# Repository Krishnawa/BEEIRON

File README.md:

# BEEIRON
A JBC soldering station

You can see the BOM file by [clicking here](https://rawcdn.githack.com/Krishnawa/BEEIRON/8fc64078c1fd5ed8496f45e8a351d78156f50b11/BEEIRON%20v0.0.3/bom/ibom.html)

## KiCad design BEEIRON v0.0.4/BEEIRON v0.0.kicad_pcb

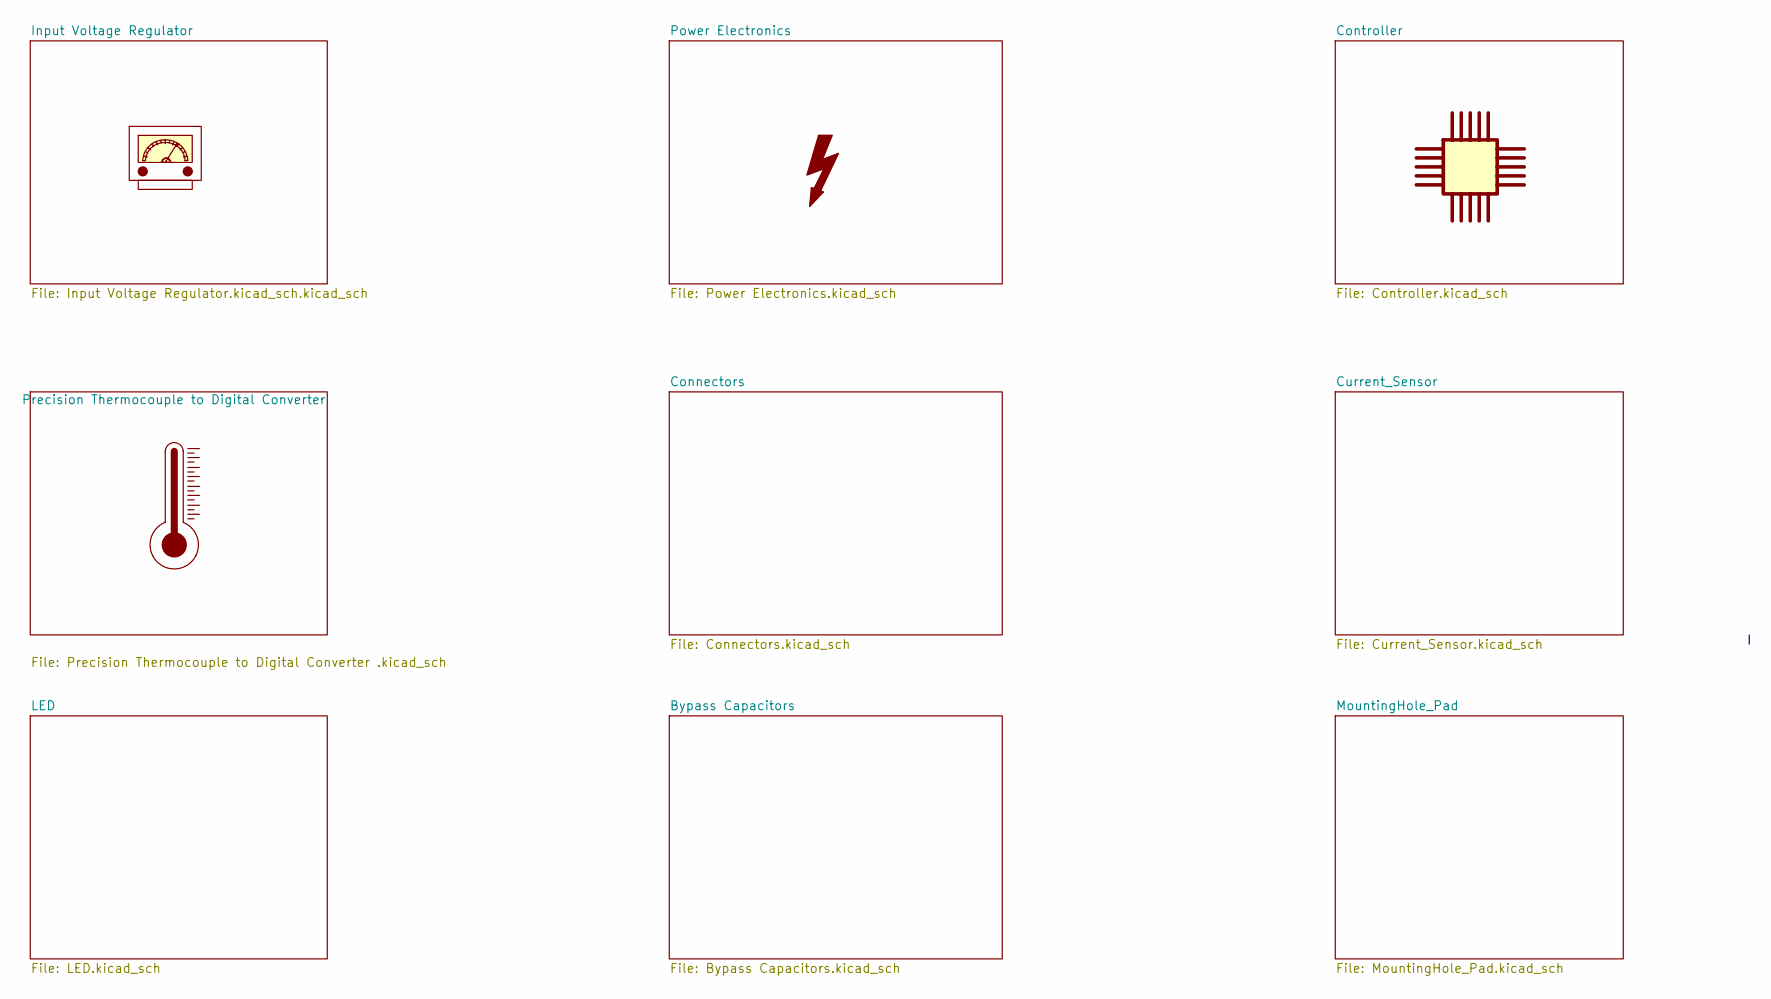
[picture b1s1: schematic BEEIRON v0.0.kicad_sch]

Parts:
MCU1: MCU; SolderJumper-2_P1.3mm_Open_TrianglePad1.0x1.5mm
U1: Regulator
U2: ThermoMeter

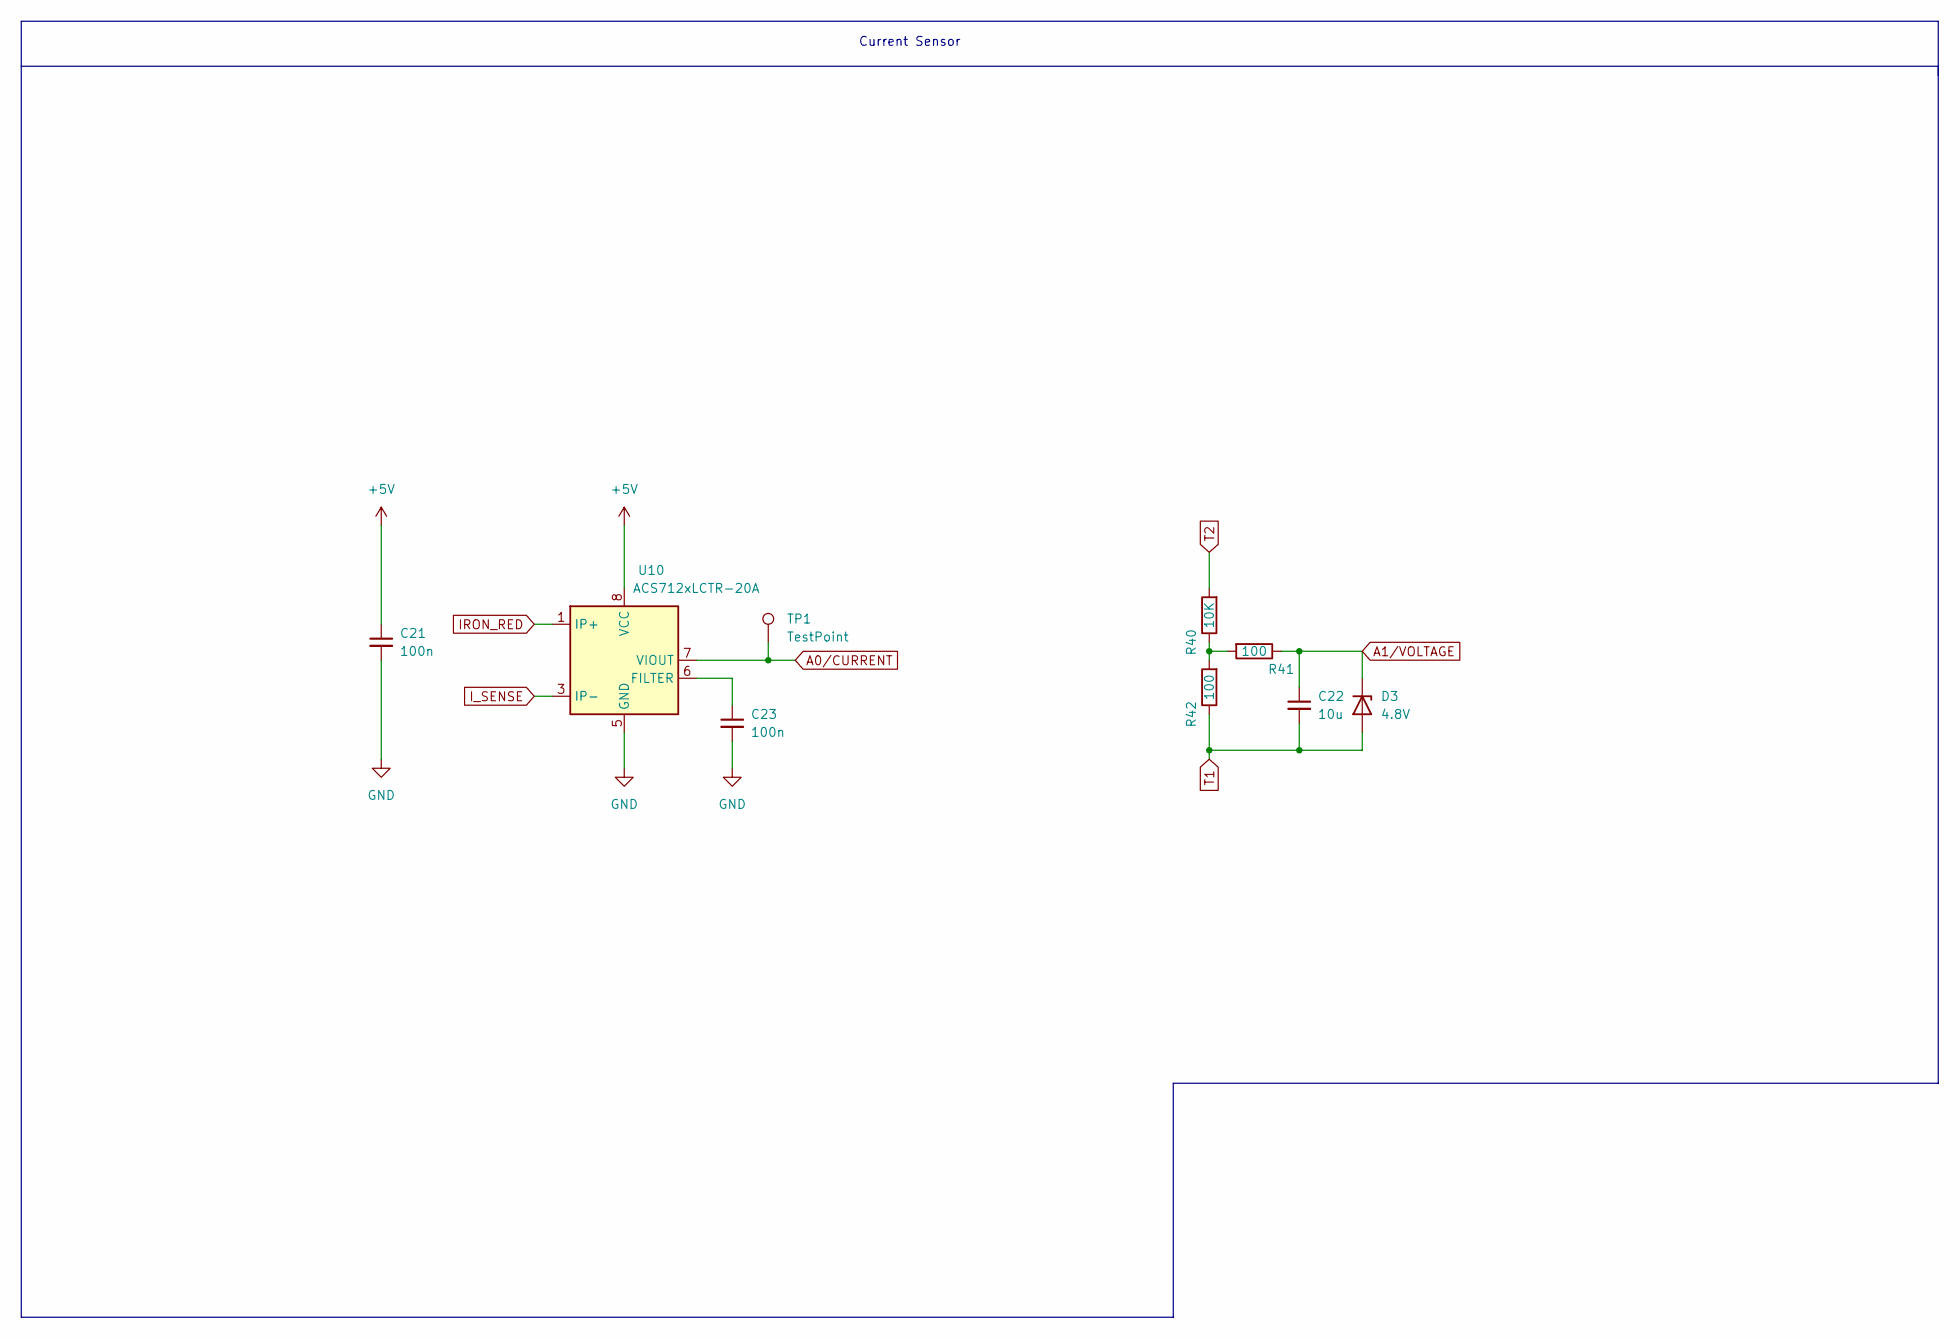
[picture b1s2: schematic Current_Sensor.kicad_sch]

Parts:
C21, C23: 100n; C_0805_2012Metric
C22: 10u; C_0805_2012Metric
D3: 4.8V; D_DO-35_SOD27_P10.16mm_Horizontal
R40: 10K; R_0805_2012Metric
R41, R42: 100; R_0805_2012Metric
TP1: TestPoint; TestPoint_Pad_2.5x2.5mm
U10: ACS712xLCTR-20A; SOIC-8_3.9x4.9mm_P1.27mm

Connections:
+5V: C21.1, U10.8 (VCC); also elsewhere on the board
A0/CURRENT: TP1.1, U10.7 (VIOUT); also elsewhere on the board
A1/VOLTAGE: C22.1, D3.1 (K), R41.1; also elsewhere on the board
GND: C21.2, C23.2, U10.5 (GND); also elsewhere on the board
IRON_RED: U10.1 (IP+), U10.2 (IP+); also elsewhere on the board
I_SENSE: U10.3 (IP-), U10.4 (IP-); also elsewhere on the board
unnamed: C23.1, U10.6 (FILTER)
unnamed: R40.1, R41.2, R42.2
T1: C22.2, D3.2 (A), R42.1; also elsewhere on the board
T2: R40.2; also elsewhere on the board

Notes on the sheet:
Current Sensor

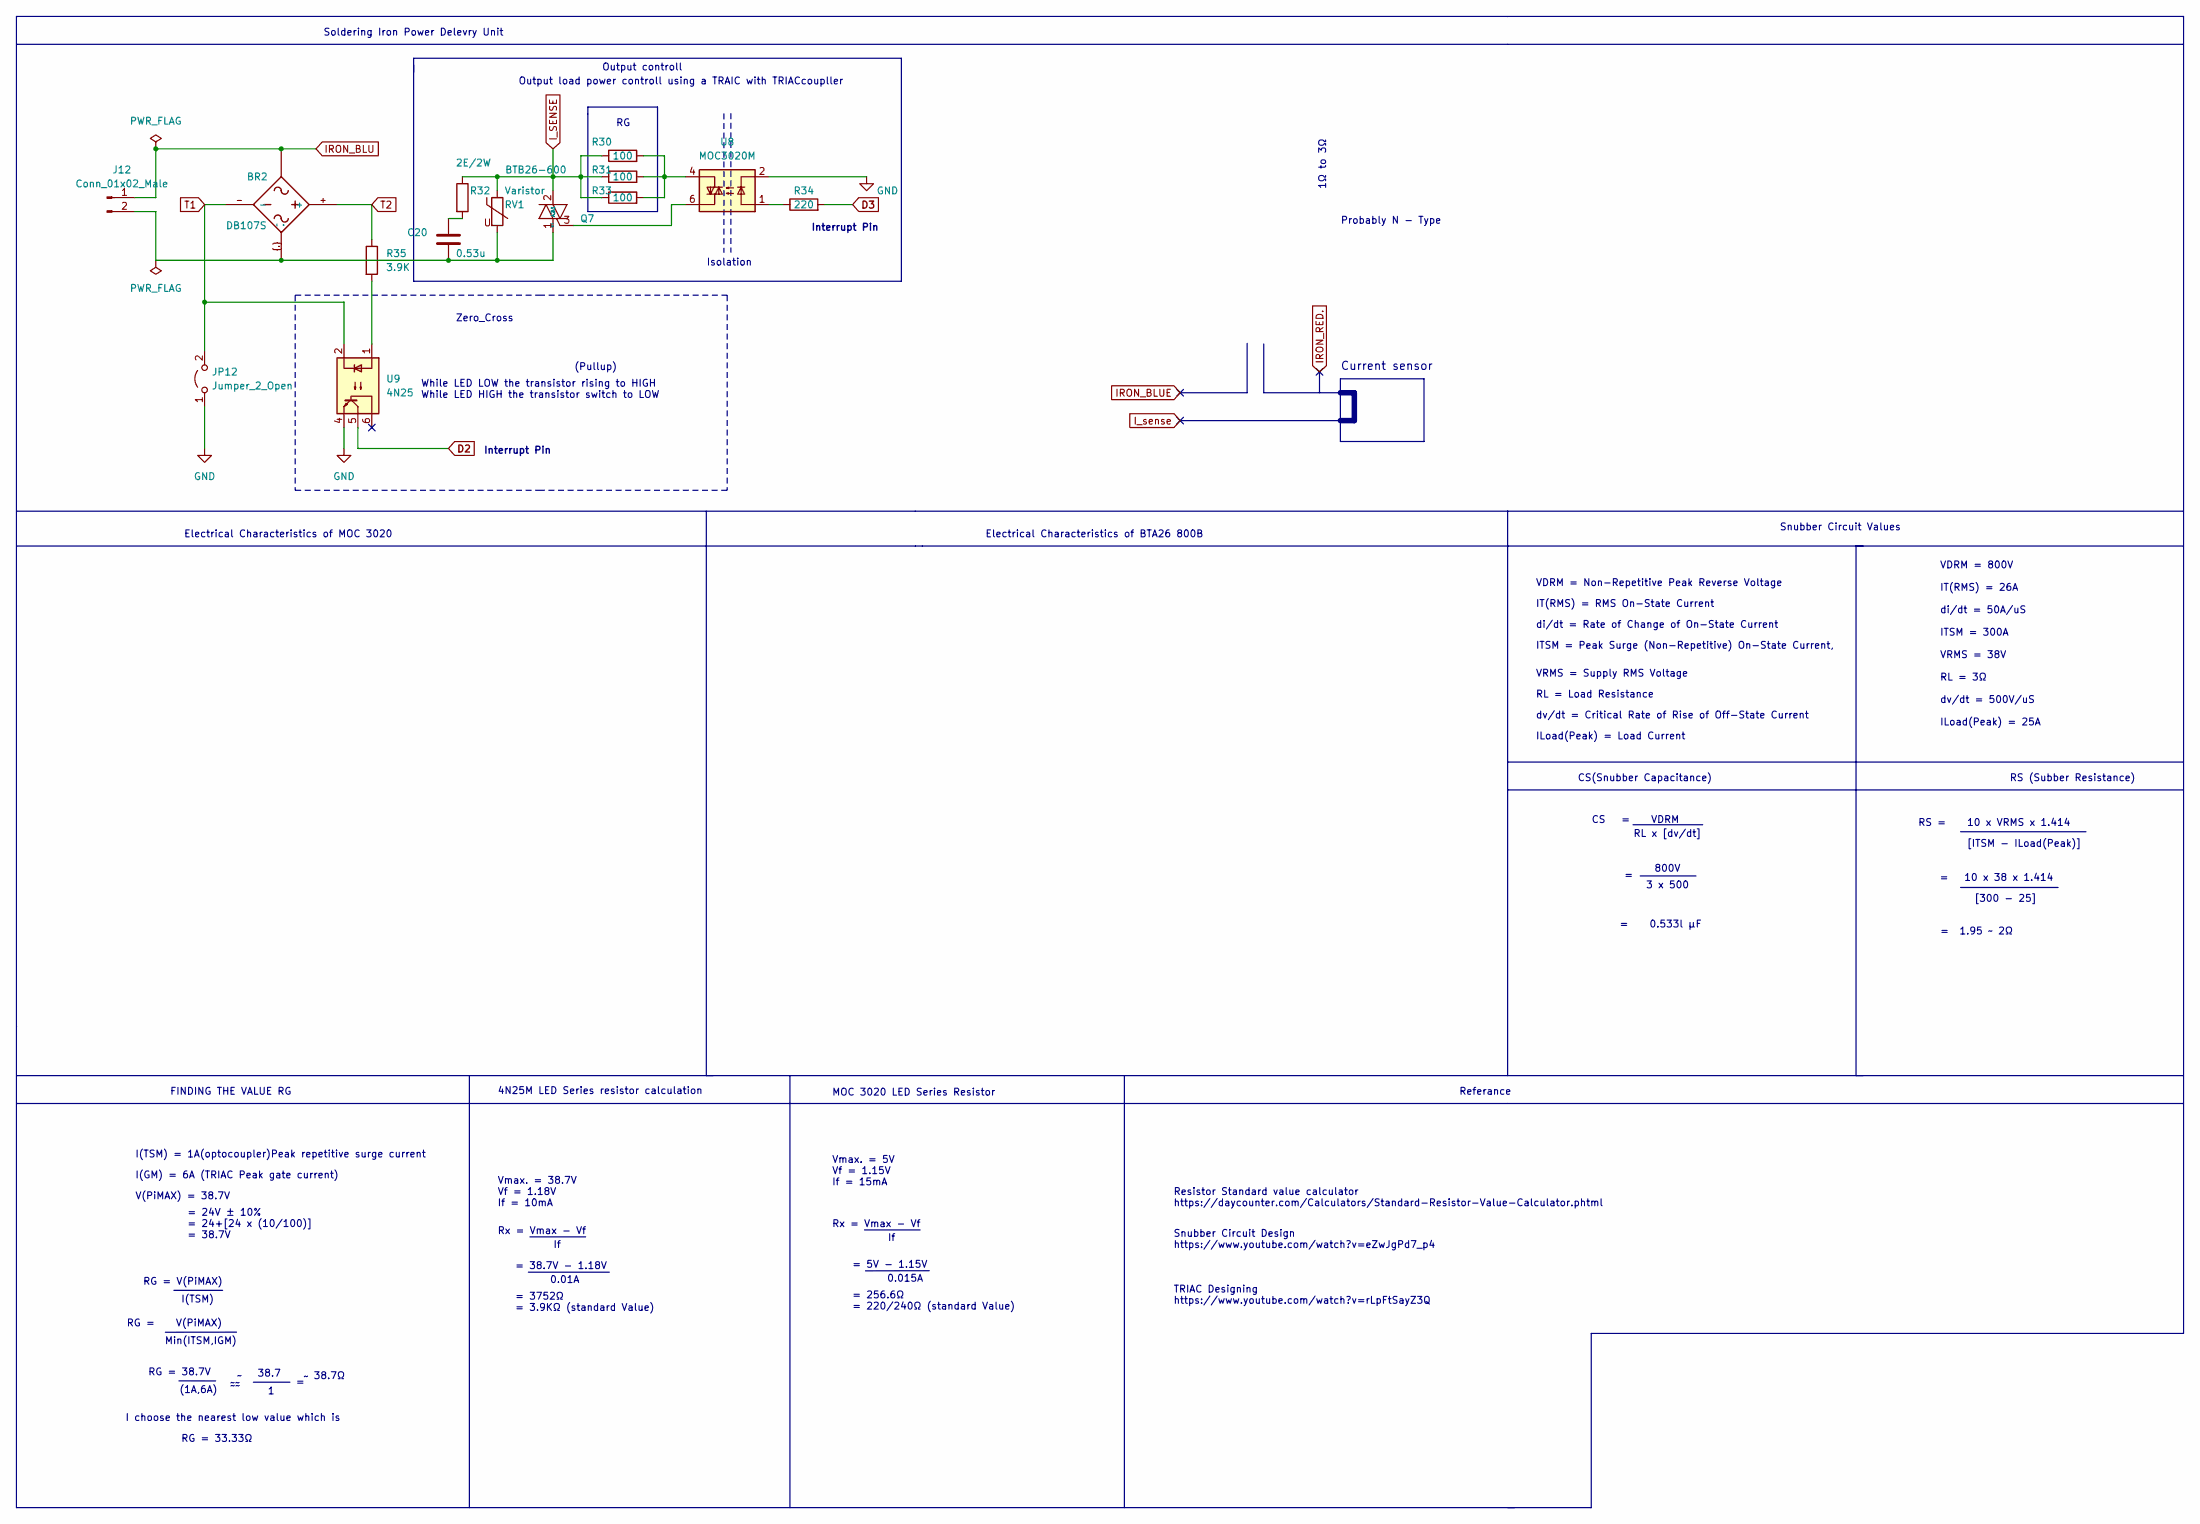
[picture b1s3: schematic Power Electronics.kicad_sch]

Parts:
BR2: DB107S; DIOB_DB107S
C20: 0.53u; C_Disc_D9.0mm_W5.0mm_P10.00mm
J12: Conn_01x02_Male; PhoenixContact_MSTBVA_2,5_2-G_1x02_P5.00mm_Vertical
JP12: Jumper_2_Open; SolderJumper-2_P1.3mm_Open_TrianglePad1.0x1.5mm
Q7: BTB26-600; TO-3P-3_Vertical
R30, R31, R33: 100; R_0805_2012Metric
R32: 2E/2W; R_Axial_DIN0411_L9.9mm_D3.6mm_P7.62mm_Vertical
R34: 220; R_0805_2012Metric
R35: 3.9K; R_0805_2012Metric
RV1: Varistor; RV_Disc_D12mm_W5.1mm_P7.5mm
U8: MOC3020M; DIP-6_W7.62mm_LongPads
U9: 4N25; DIP-6_W7.62mm

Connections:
D2: U9.5; also elsewhere on the board
D3: R34.2; also elsewhere on the board
GND: JP12.1 (A), U8.2, U9.4; also elsewhere on the board
IRON_BLU: BR2.~, BR2.~~, J12.1; also elsewhere on the board
I_SENSE: Q7.2 (A2), R30.1, R31.1, R32.1, R33.1, RV1.1; also elsewhere on the board
unnamed: BR2.~{.}, C20.2, J12.2, Q7.1 (A1), RV1.2
unnamed: C20.1, R32.2
unnamed: Q7.3 (G), U8.6
unnamed: R30.2, R31.2, R33.2, U8.4
unnamed: R34.1, U8.1
unnamed: R35.2, U9.1
T1: BR2.-, JP12.2 (B), U9.2; also elsewhere on the board
T2: BR2.+, R35.1; also elsewhere on the board

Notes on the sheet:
= 38.7V - 1.18V
Soldering Iron Power Delevry Unit
I(TSM) = 1A(optocoupler)Peak repetitive surge current
Output controll
= 3752Ω = 3.9KΩ (standard Value)
CS(Snubber Capacitance)
1Ω to 3Ω
Output load power controll using a TRAIC with TRIACcoupller
RL x [dv/dt]
VRMS = Supply RMS Voltage
Snubber Circuit Design https://www.youtube.com/watch?v=eZwJgPd7_p4
Rx = Vmax - Vf
0.015A
VDRM = Non−Repetitive Peak Reverse Voltage
RS (Subber Resistance)
FINDING THE VALUE RG
Resistor Standard value calculator https://daycounter.com/Calculators/Standard-Resistor-Value-Calculator.phtml
di/dt = Rate of Change of On−State Current
I choose the nearest low value which is
I(GM) = 6A (TRIAC Peak gate current)
IT(RMS) = RMS On−State Current
Zero_Cross
Isolation
I(TSM)
Referance
Min(ITSM,IGM)
CS = VDRM
VDRM = 800V IT(RMS) = 26A di/dt = 50A/uS ITSM = 300A VRMS = 38V RL = 3Ω dv/dt = 500V/uS ILoad(Peak) = 25A
(1A,6A)
RG = V(PiMAX)
RG = 33.33Ω
38.7
= 5V - 1.15V
Probably N - Type
[ITSM - ILoad(Peak)]
RL = Load Resistance
Current sensor
Interrupt Pin
ILoad(Peak) = Load Current
V(PiMAX) = 38.7V

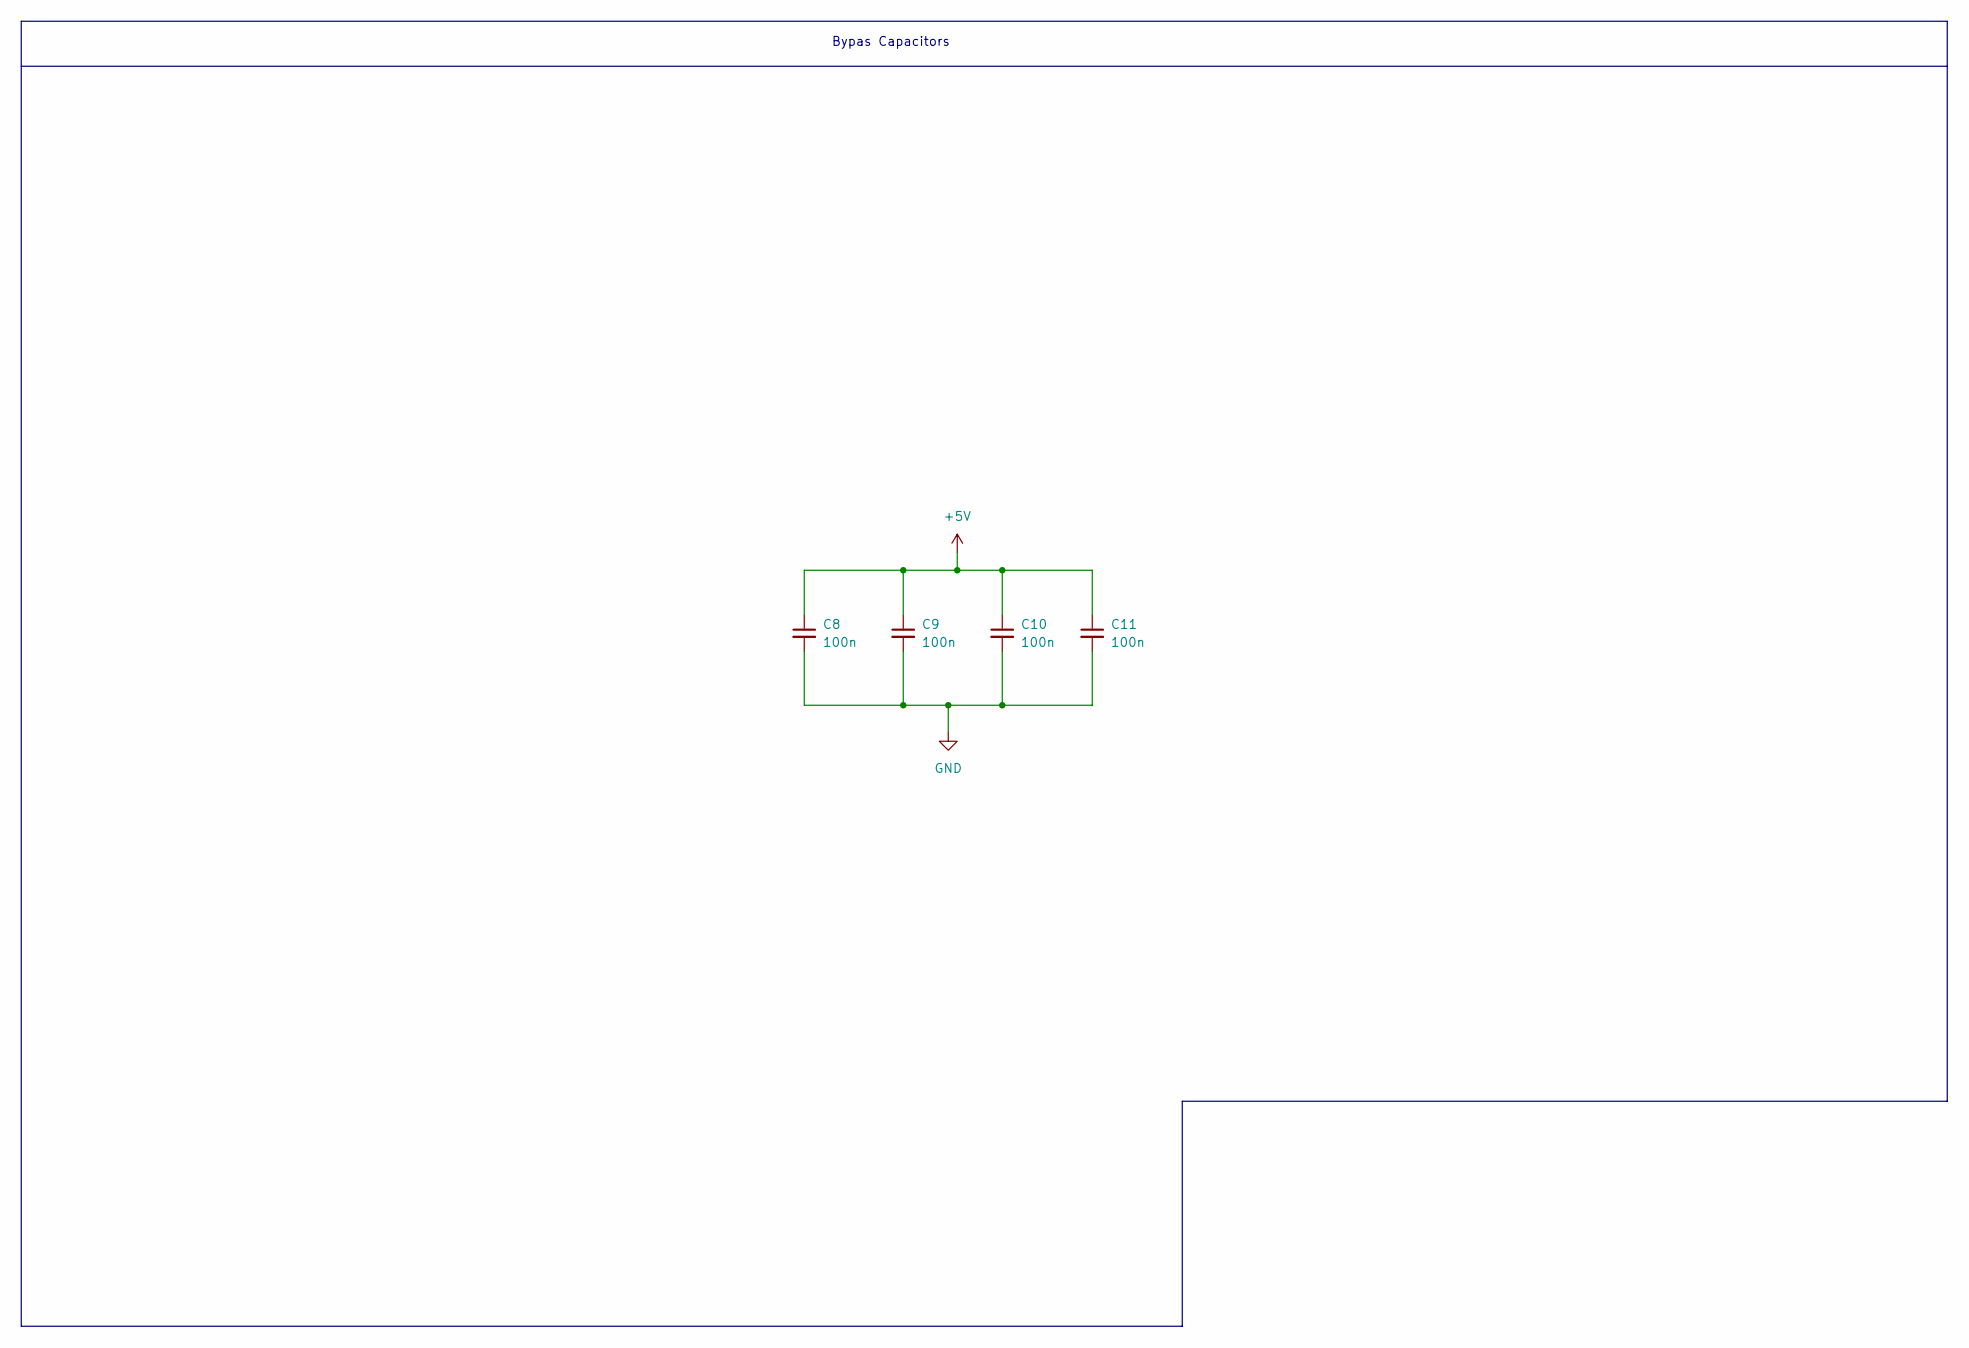
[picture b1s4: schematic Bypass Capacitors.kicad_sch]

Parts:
C8, C9, C10, C11: 100n; C_0805_2012Metric

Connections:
+5V: C8.1, C9.1, C10.1, C11.1; also elsewhere on the board
GND: C8.2, C9.2, C10.2, C11.2; also elsewhere on the board

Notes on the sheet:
Bypas Capacitors

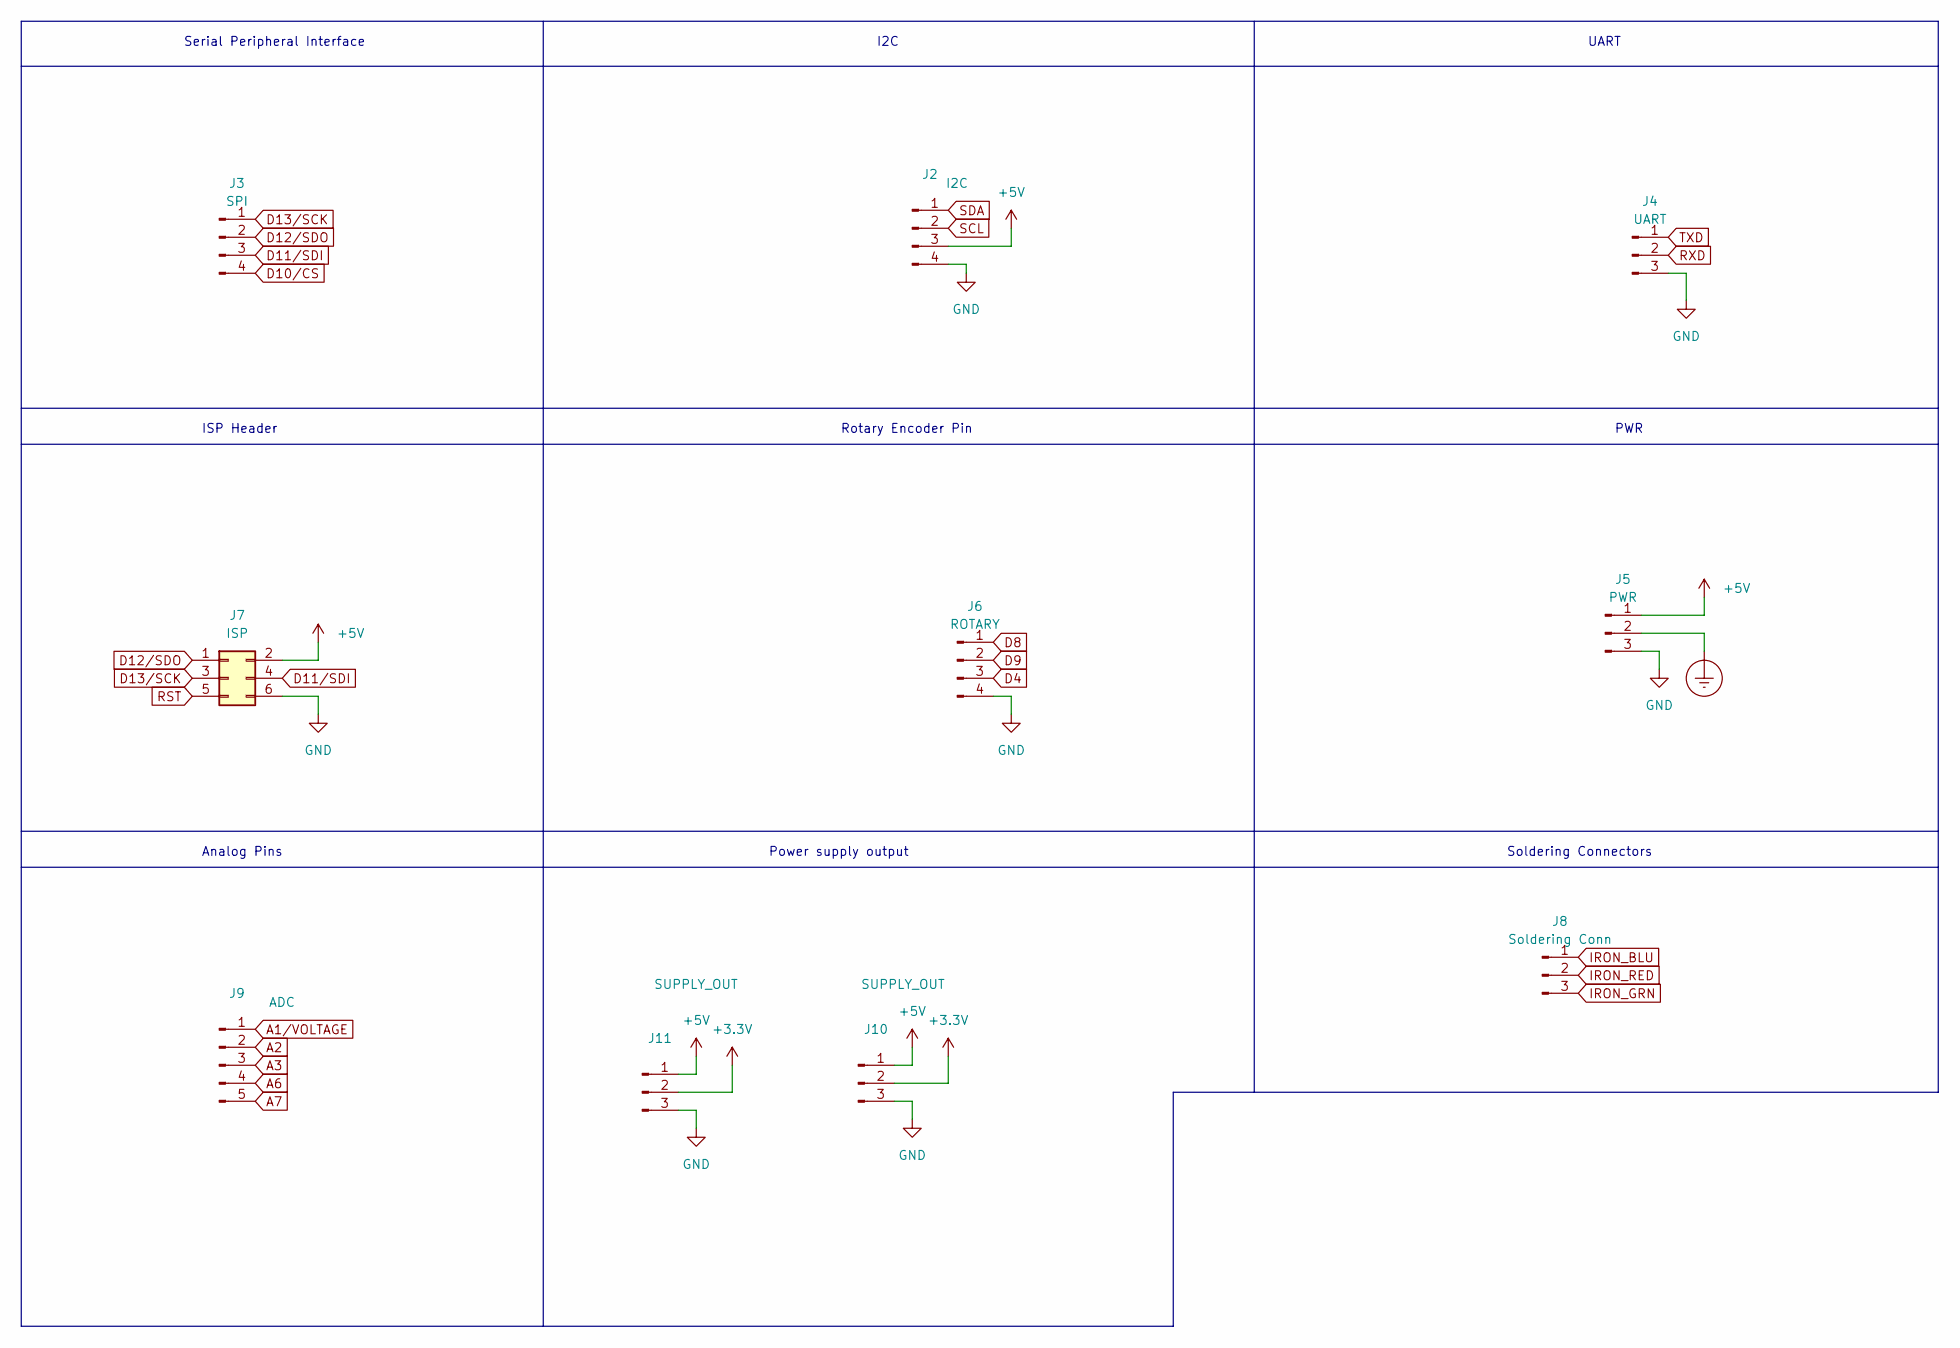
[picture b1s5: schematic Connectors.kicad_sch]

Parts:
J2: I2C; PinHeader_1x04_P2.54mm_Vertical
J3: SPI; PinHeader_1x04_P2.54mm_Vertical
J4: UART; PinHeader_1x03_P2.54mm_Vertical
J5: PWR; PinHeader_1x03_P2.54mm_Vertical
J6: ROTARY; PinHeader_1x04_P2.54mm_Vertical
J7: ISP; PinHeader_2x03_P2.54mm_Vertical
J8: Soldering Conn; PhoenixContact_MSTBVA_2,5_3-G-5,08_1x03_P5.08mm_Vertical
J9: ADC; PinHeader_1x05_P2.54mm_Vertical
J10, J11: SUPPLY_OUT; PinHeader_1x03_P2.54mm_Vertical

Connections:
+3V3: J10.2, J11.2; also elsewhere on the board
+5V: J2.3, J5.1, J7.2, J10.1, J11.1; also elsewhere on the board
A1/VOLTAGE: J9.1; also elsewhere on the board
A2: J9.2; also elsewhere on the board
A3: J9.3; also elsewhere on the board
A6: J9.4; also elsewhere on the board
A7: J9.5; also elsewhere on the board
D4: J6.3; also elsewhere on the board
D8: J6.1; also elsewhere on the board
D9: J6.2; also elsewhere on the board
D10/CS: J3.4; also elsewhere on the board
D11/SDI: J3.3, J7.4; also elsewhere on the board
D12/SDO: J3.2, J7.1; also elsewhere on the board
D13/SCK: J3.1, J7.3; also elsewhere on the board
Earth_Protective: J5.2; also elsewhere on the board
GND: J2.4, J4.3, J5.3, J6.4, J7.6, J10.3, J11.3; also elsewhere on the board
IRON_BLU: J8.1; also elsewhere on the board
IRON_GRN: J8.3; also elsewhere on the board
IRON_RED: J8.2; also elsewhere on the board
RST: J7.5; also elsewhere on the board
RXD: J4.2; also elsewhere on the board
SCL: J2.2; also elsewhere on the board
SDA: J2.1; also elsewhere on the board
TXD: J4.1; also elsewhere on the board

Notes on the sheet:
I2C
ISP Header
Rotary Encoder Pin
UART
Power supply output
Soldering Connectors
Analog Pins
Serial Peripheral Interface
PWR

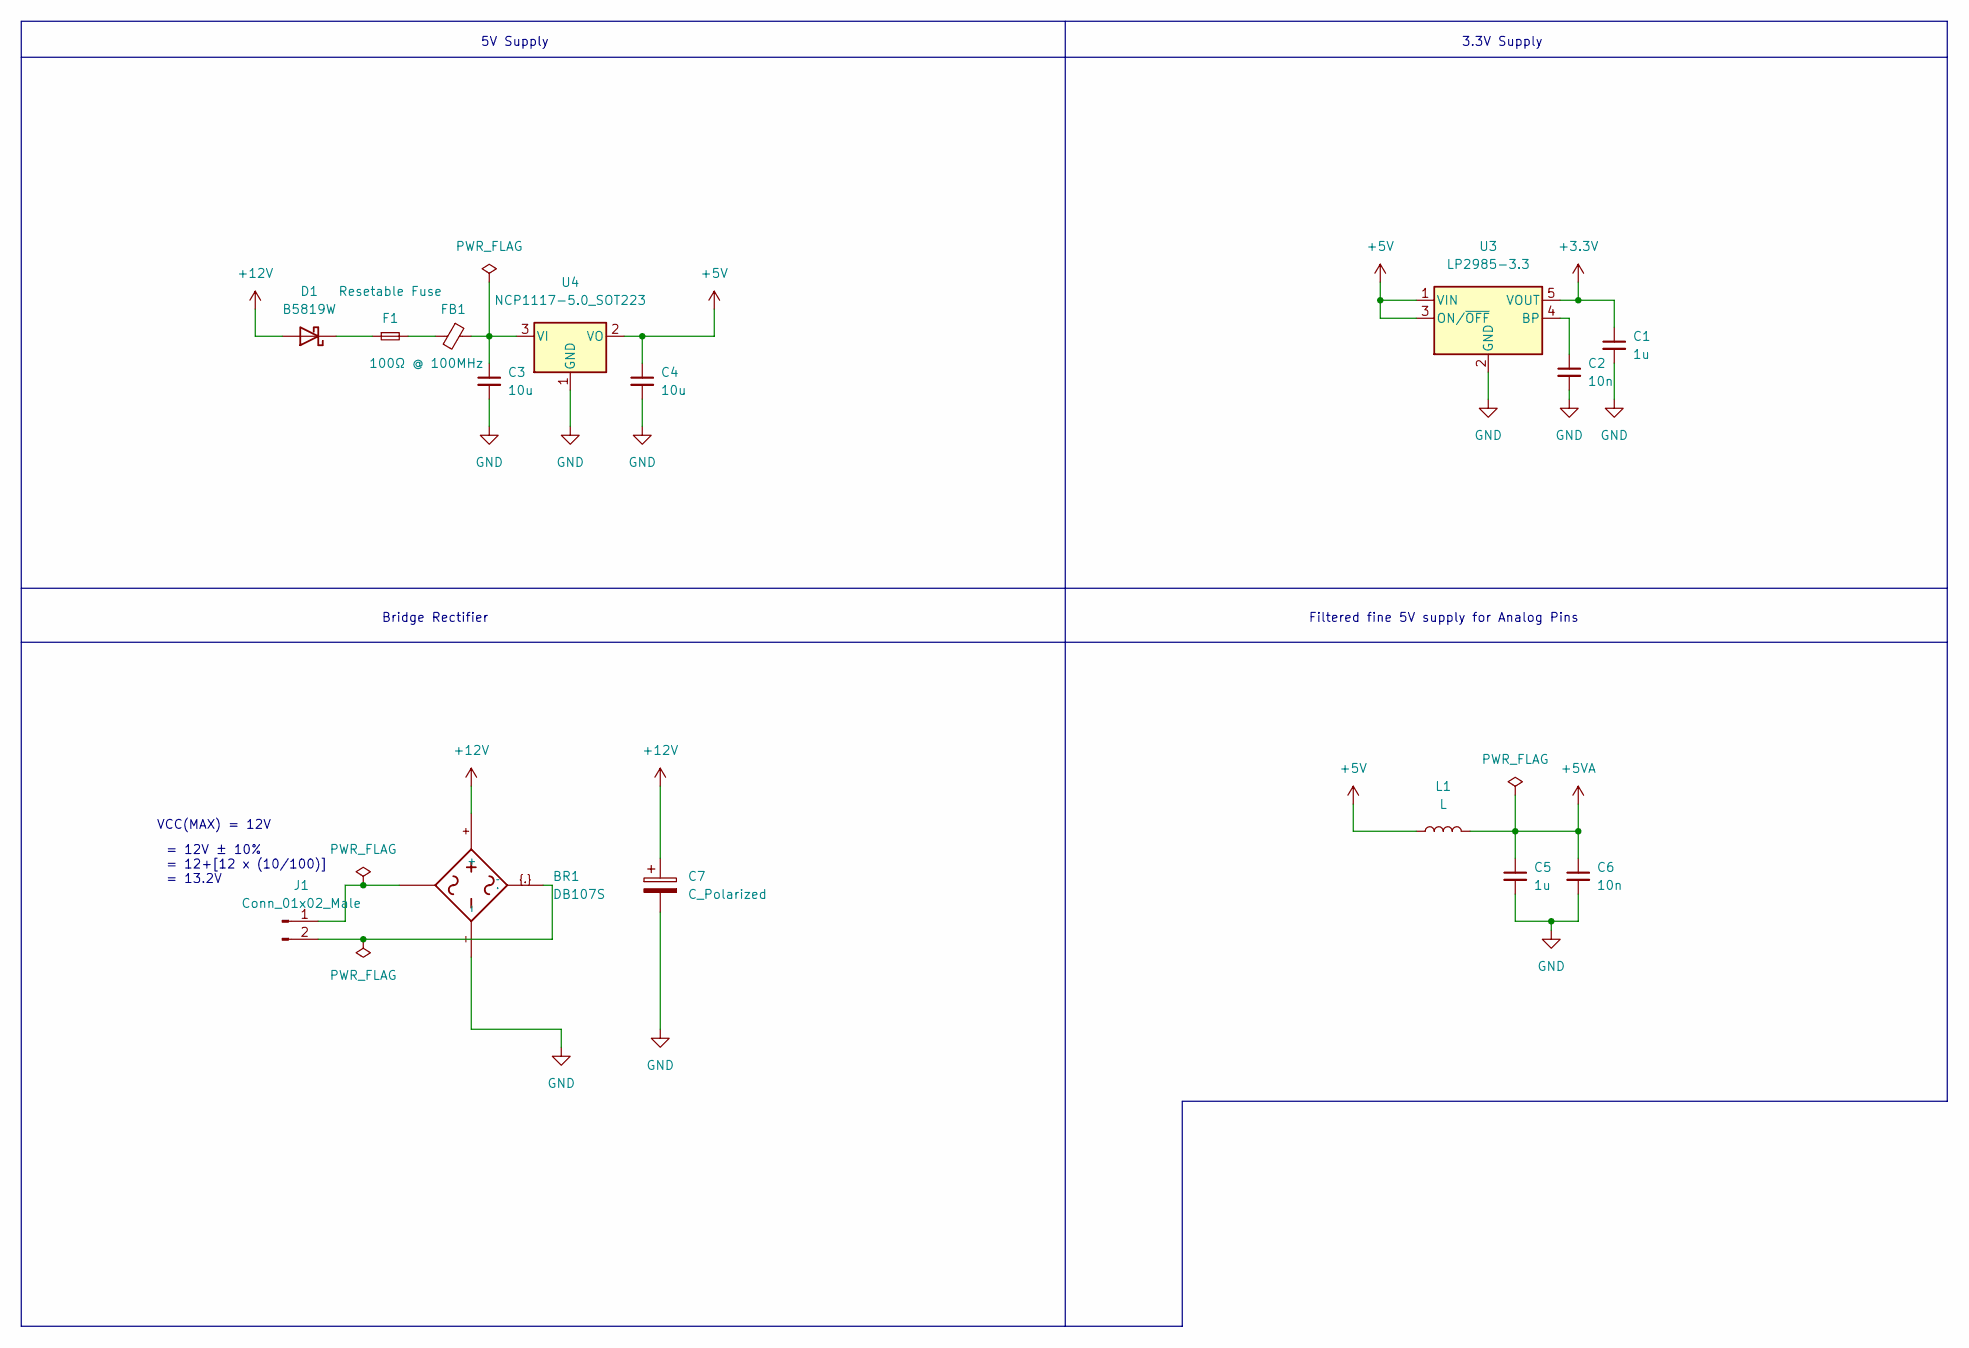
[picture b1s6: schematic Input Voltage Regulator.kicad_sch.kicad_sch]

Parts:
BR1: DB107S; DIOB_DB107S
C1, C5: 1u; C_0805_2012Metric
C2, C6: 10n; C_0805_2012Metric
C3, C4: 10u; C_0805_2012Metric
C7: C_Polarized; C_Radial_D8.0mm_H7.0mm_P3.50mm
D1: B5819W; D_SOD-123
F1: Resetable Fuse; Fuse_1206_3216Metric
FB1: 100Ω @ 100MHz; L_0603_1608Metric
J1: Conn_01x02_Male; PinHeader_1x02_P2.54mm_Vertical
L1: L; L_0603_1608Metric
U3: LP2985-3.3; SOT-23-5
U4: NCP1117-5.0_SOT223; SOT-223-3_TabPin2

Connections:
+3V3: C1.1, U3.5 (VOUT); also elsewhere on the board
+5V: C4.1, L1.1, U3.1 (VIN), U3.3 (ON/~OFF), U4.2 (VO); also elsewhere on the board
+5VA: C5.1, C6.1, L1.2; also elsewhere on the board
+12V: BR1.+, C7.1, D1.2 (A)
GND: BR1.-, C1.2, C2.2, C3.2, C4.2, C5.2, C6.2, C7.2, U3.2 (GND), U4.1 (GND); also elsewhere on the board
unnamed: BR1.~, J1.1
unnamed: BR1.~{.}, J1.2
unnamed: C2.1, U3.4 (BP)
unnamed: C3.1, FB1.1, U4.3 (VI)
unnamed: D1.1 (K), F1.1
unnamed: F1.2, FB1.2

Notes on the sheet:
Filtered fine 5V supply for Analog Pins
Bridge Rectifier
5V Supply
= 12V ± 10% = 12+[12 x (10/100)] = 13.2V
3.3V Supply
VCC(MAX) = 12V

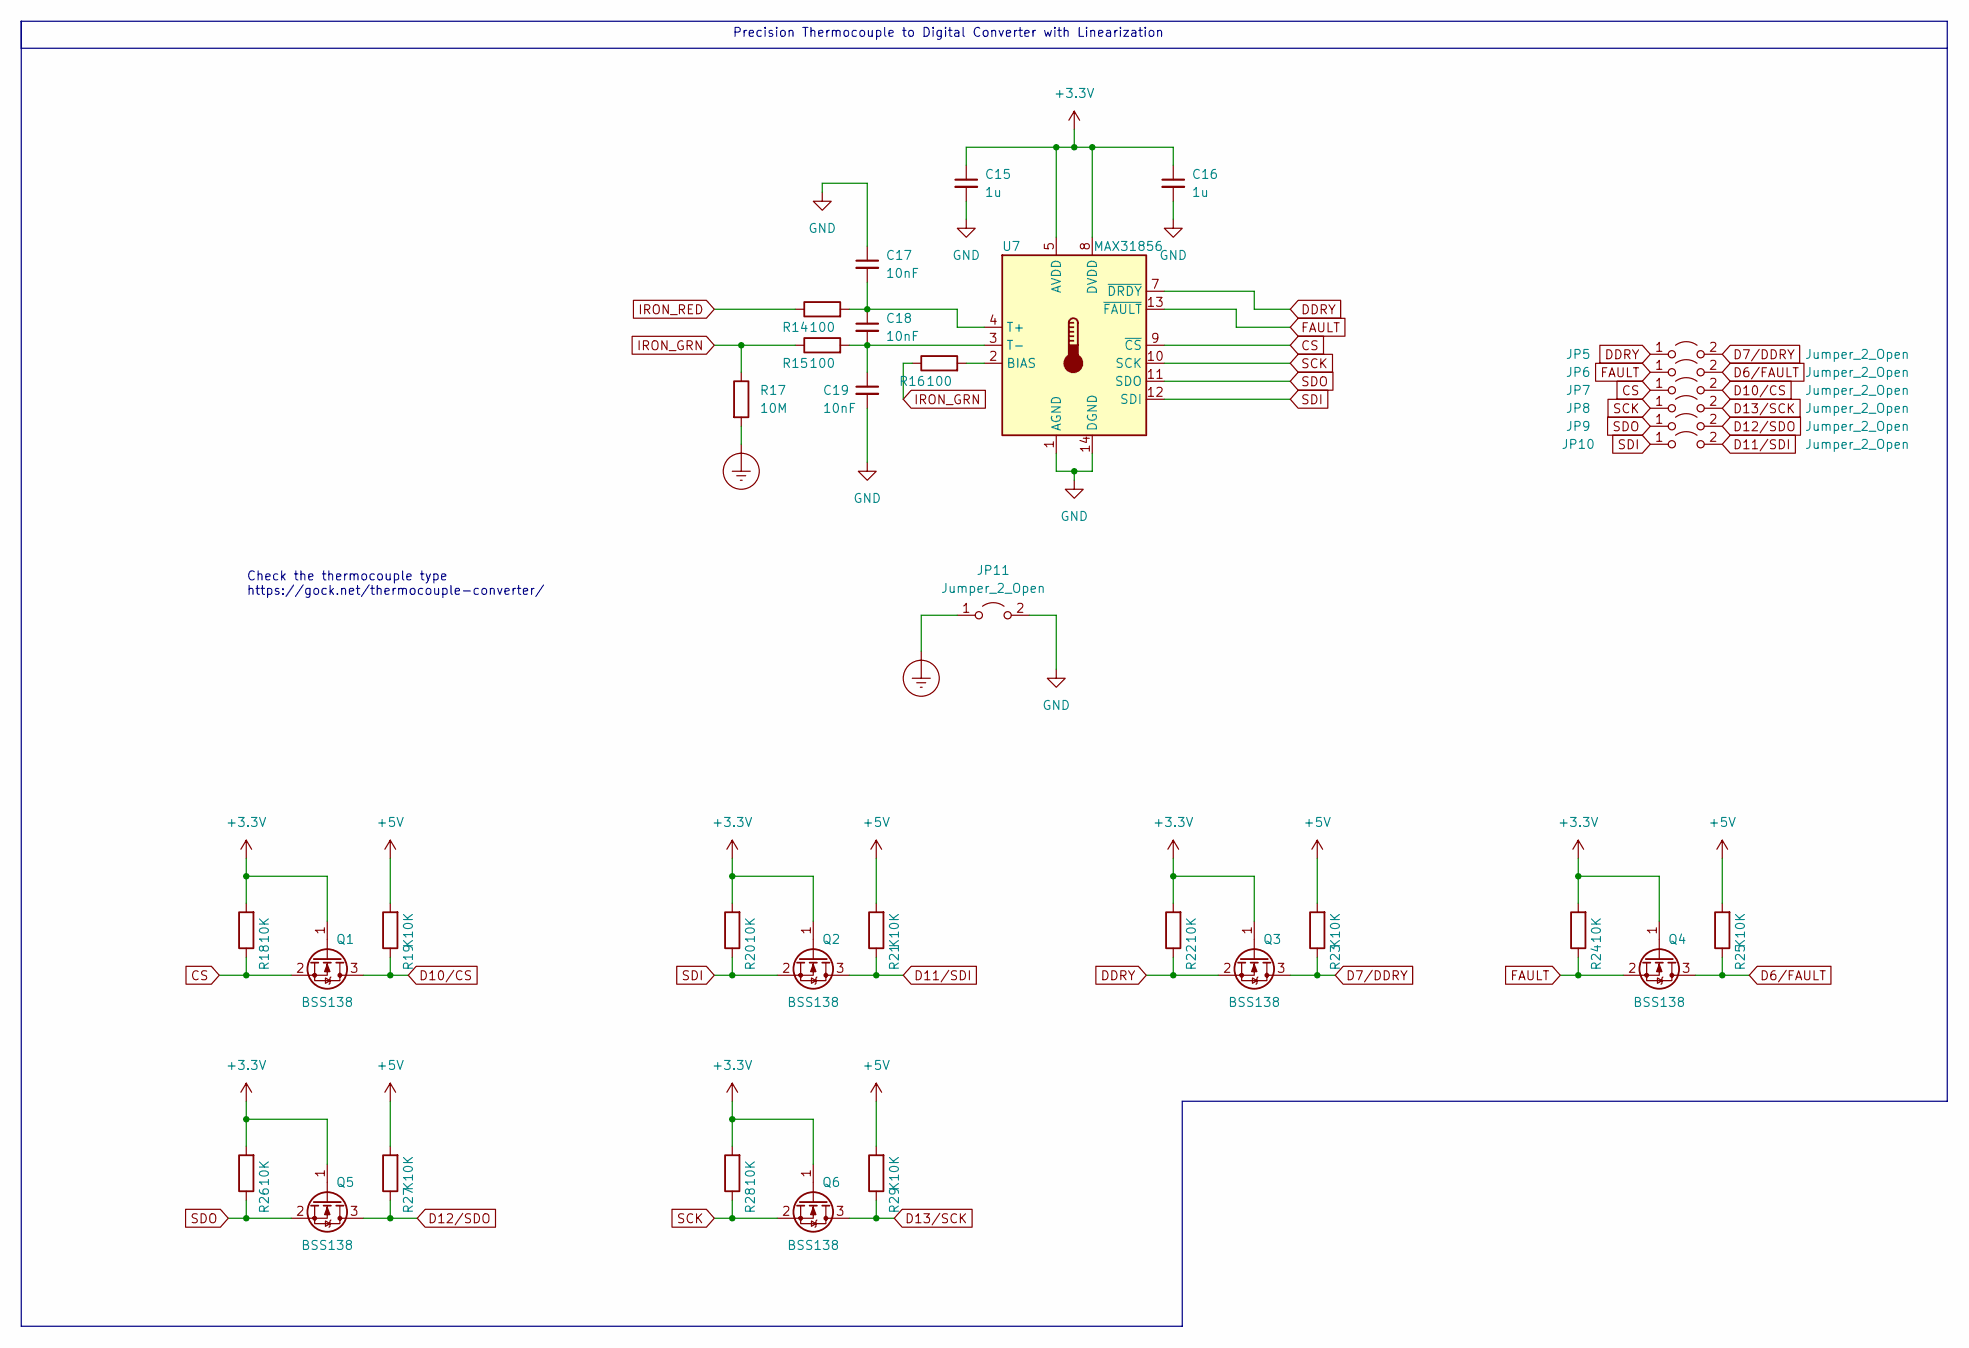
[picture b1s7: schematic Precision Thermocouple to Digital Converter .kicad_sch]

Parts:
C15, C16: 1u; C_0805_2012Metric
C17, C18, C19: 10nF; C_0805_2012Metric
JP5, JP6, JP7, JP8, JP9, JP10, JP11: Jumper_2_Open; SolderJumper-2_P1.3mm_Open_TrianglePad1.0x1.5mm
Q1, Q2, Q3, Q4, Q5, Q6: BSS138; SOT-23
R14, R15, R16: 100; R_0805_2012Metric
R17: 10M; R_0805_2012Metric
R18, R20, R22, R24, R26, R28: 10K; R_0805_2012Metric
R19, R21, R23, R25, R27, R29: K10K; R_0805_2012Metric
U7: MAX31856; TSSOP-14_4.4x5mm_P0.65mm

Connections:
+3V3: C15.1, C16.1, Q1.1 (G), Q2.1 (G), Q3.1 (G), Q4.1 (G), Q5.1 (G), Q6.1 (G), R18.2, R20.2, R22.2, R24.2, R26.2, R28.2, U7.5 (AVDD), U7.8 (DVDD); also elsewhere on the board
+5V: R19.2, R21.2, R23.2, R25.2, R27.2, R29.2; also elsewhere on the board
CS: JP7.1 (A), Q1.2 (S), R18.1, U7.9 (~CS)
D6/FAULT: JP6.2 (B), Q4.3 (D), R25.1; also elsewhere on the board
D7/DDRY: JP5.2 (B), Q3.3 (D), R23.1; also elsewhere on the board
D10/CS: JP7.2 (B), Q1.3 (D), R19.1; also elsewhere on the board
D11/SDI: JP10.2 (B), Q2.3 (D), R21.1; also elsewhere on the board
D12/SDO: JP9.2 (B), Q5.3 (D), R27.1; also elsewhere on the board
D13/SCK: JP8.2 (B), Q6.3 (D), R29.1; also elsewhere on the board
DDRY: JP5.1 (A), Q3.2 (S), R22.1, U7.7 (~DRDY)
Earth_Protective: JP11.1 (A), R17.2; also elsewhere on the board
FAULT: JP6.1 (A), Q4.2 (S), R24.1, U7.13 (~FAULT)
GND: C15.2, C16.2, C17.1, C19.2, JP11.2 (B), U7.1 (AGND), U7.14 (DGND); also elsewhere on the board
IRON_GRN: R15.1, R16.1, R17.1; also elsewhere on the board
IRON_RED: R14.1; also elsewhere on the board
unnamed: C17.2, C18.1, R14.2, U7.4 (T+)
unnamed: C18.2, C19.1, R15.2, U7.3 (T-)
unnamed: R16.2, U7.2 (BIAS)
SCK: JP8.1 (A), Q6.2 (S), R28.1, U7.10 (SCK)
SDI: JP10.1 (A), Q2.2 (S), R20.1, U7.12 (SDI)
SDO: JP9.1 (A), Q5.2 (S), R26.1, U7.11 (SDO)

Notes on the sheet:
Precision Thermocouple to Digital Converter with Linearization
Check the thermocouple type https://gock.net/thermocouple-converter/
